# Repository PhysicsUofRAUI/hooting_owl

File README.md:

# hooting_owl
Hold code and eventually the pcb layout for my hooting owl retrofit

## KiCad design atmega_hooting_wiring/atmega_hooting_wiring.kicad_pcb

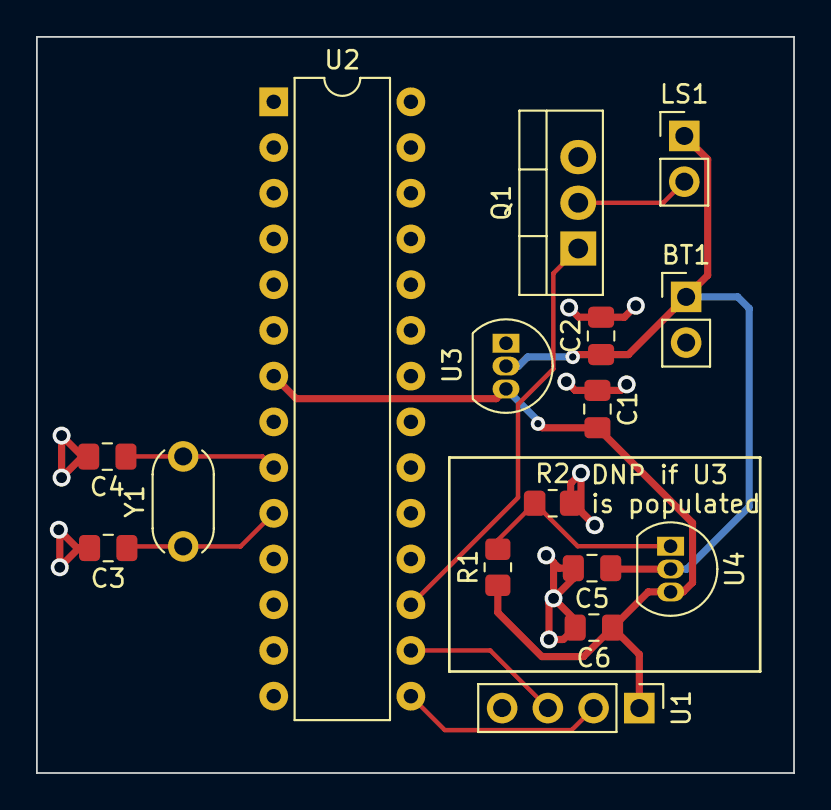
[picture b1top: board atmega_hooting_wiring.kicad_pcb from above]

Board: 2 copper layers, 42.1 x 40.9 mm, 16 parts (0 on the bottom side), 10 nets.

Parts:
BT1: Battery; PinHeader_1x02_P2.54mm_Vertical
C1, C2: 1u; C_0805_2012Metric_Pad1.18x1.45mm_HandSolder
C3, C4: 22p; C_0805_2012Metric_Pad1.18x1.45mm_HandSolder
C5, C6: 0.1u; C_0805_2012Metric_Pad1.18x1.45mm_HandSolder
LS1: Speaker; PinHeader_1x02_P2.54mm_Vertical
Q1: TIP122; TO-220-3_Vertical
R1: 27k; R_0805_2012Metric_Pad1.20x1.40mm_HandSolder
R2: 75k; R_0805_2012Metric_Pad1.20x1.40mm_HandSolder
U1: PinHeader_1x04_P2.54mm_Vertical
U2: ATmega328-P; DIP-28_W7.62mm
U3: MCP1700x-500xxTO; TO-92_Inline
U4: LM317L_TO92; TO-92_Inline
Y1: Crystal; Resonator-2Pin_W6.0mm_H3.0mm

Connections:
unnamed: Q1.1 (B), U2.17 (PB3)
unnamed: LS1.2, Q1.2 (C)
unnamed: U1.3 (Echo), U2.16 (PB2)
unnamed: U1.2 (Trig), U2.15 (PB1)
unnamed: C4.1, U2.9 (XTAL1/PB6), Y1.2
unnamed: C3.1, U2.10 (XTAL2/PB7), Y1.1
unnamed: R1.2, R2.1, U4.1 (ADJ)
VCC: C1.2, C6.1, R1.1, U1.1 (Vcc), U2.7 (VCC), U3.3 (VO), U4.3 (VO)
batt_+: BT1.1 (+), C2.1, C5.1, LS1.1, U3.2 (VI), U4.2 (VI)
batt_-: BT1.2 (-), C1.1, C2.2, C3.2, C4.2, C5.2, C6.2, Q1.3 (E), R2.2, U1.4 (GND), U2.8 (GND), U2.22 (GND), U3.1 (GND)

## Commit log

2023-06-03 Add simple arduino prox. buzzer example
2023-07-01 update tone
2023-07-01 add owl hooting arduino code
2023-07-01 Add kicad files for the ATMEGA328 and speaker accompanying it.
2023-07-01 add gitignore
2023-08-02 add pcb and wiring schematic for production
